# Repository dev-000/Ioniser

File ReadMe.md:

# Build an Ioniser in under $10

This repo contains all the hardware files needed to build a low cost ioniser. It helps in settling dust particles around the device, effectively "cleansing" the air in the room.  Repo also contains the simulation files if you want to check the theoretical output voltages.

Details and circuit explanations are mentioned in the link below. Please do read the links fully before starting the build process. 
 - [http://amaldev.blog/build-ioniser-in-under-10-dollars/](http://amaldev.blog/build-ioniser-in-under-10-dollars/)
 - [http://amaldev.blog/build-an-ioniser-in-under-10-dollars-part-2/](http://amaldev.blog/build-an-ioniser-in-under-10-dollars-part-2/)

Repo contains files for both Positive and Negative Ioniser which gives you a High Voltage positive and negative DC voltages. The circuits are very similar except that the diodes are swapped. Bill of Materials remains same for both versions. 

You can upload the *Gerbers.zip* file directly on to any online PCB manufacturing shop to get it made or edit the Eagle schematic and layout files to your liking.   

Please be very careful dealing with AC voltages and High voltage DC outputs. Capacitors do retain charge for sometime and you will get a zap if you touch them. 

**License:** Released as open source hardware. Do whatever you want with it. :smiley:

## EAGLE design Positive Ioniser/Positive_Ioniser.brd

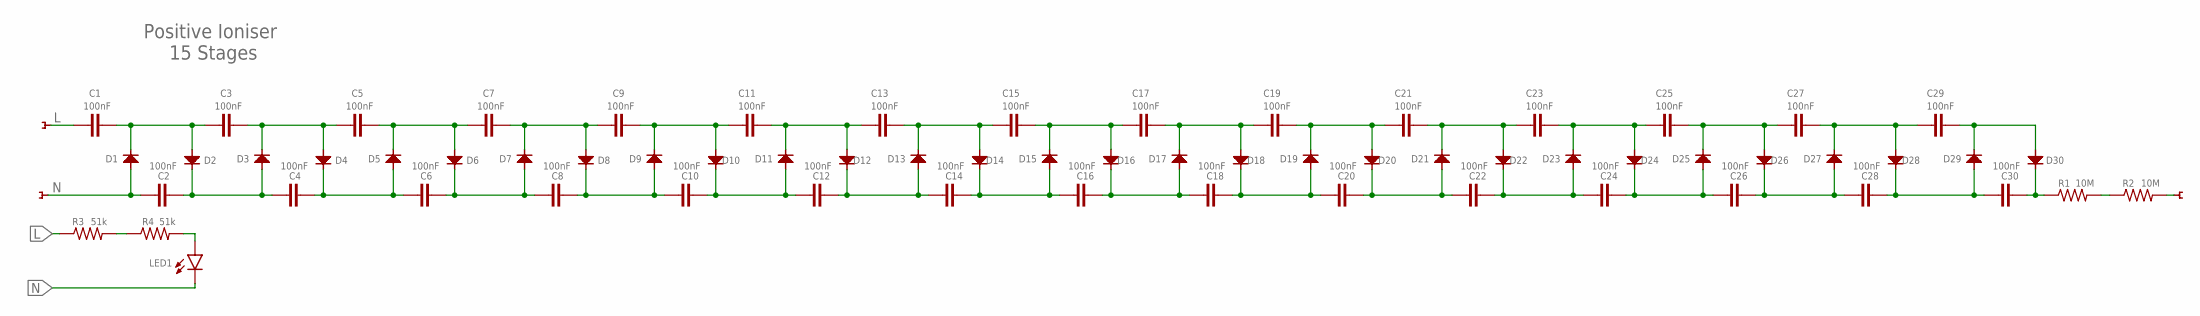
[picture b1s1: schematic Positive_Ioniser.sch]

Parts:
C1, C2, C3, C4, C5, C6, C7, C8, C9, C10, C11, C12, C13, C14, C15, C16, C17, C18, C19, C20, C21, C22, C23, C24, C25, C26, C27, C28, C29, C30: 100nF; C1812; TOLERANCE ±10%; PART-NUM 1812B104K631CT
D1, D2, D3, D4, D5, D6, D7, D8, D9, D10, D11, D12, D13, D14, D15, D16, D17, D18, D19, D20, D21, D22, D23, D24, D25, D26, D27, D28, D29, D30: DIODE-1N4007; DO-214A; PART-NUM 1N4007G
LED1: LED-0603-SMD; LED-0603; PART-NUM D-060306R1/SS2/L
R1, R2: 10M; R1206; TOLERANCE ±1%; PART-NUM 1206W4F1005T5E
R3, R4: 51k; R1210; TOLERANCE ±5%; PART-NUM CR1210J51K0P05Z
TP1, TP2: TEST-POINT5MM; SMD-SQ-PADS-5MM
TP3: TEST-POINT30X10; LONG-RECT-PAD-50MM

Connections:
L: C1.1, R3.1, TP1.P$1
N: C2.1, D1.ANODE (A), LED1.C, TP2.P$1
unnamed: C2.2, C4.1, D2.CATHODE (C), D3.ANODE (A)
unnamed: C1.2, C3.1, D1.CATHODE (C), D2.ANODE (A)
unnamed: R3.2, R4.1
unnamed: R1.2, R2.1
unnamed: C5.2, C7.1, D5.CATHODE (C), D6.ANODE (A)
unnamed: C4.2, C6.1, D4.CATHODE (C), D5.ANODE (A)
unnamed: LED1.A, R4.2
unnamed: C6.2, C8.1, D6.CATHODE (C), D7.ANODE (A)
unnamed: C3.2, C5.1, D3.CATHODE (C), D4.ANODE (A)
unnamed: C9.2, C11.1, D9.CATHODE (C), D10.ANODE (A)
unnamed: C8.2, C10.1, D8.CATHODE (C), D9.ANODE (A)
unnamed: C10.2, C12.1, D10.CATHODE (C), D11.ANODE (A)
unnamed: C7.2, C9.1, D7.CATHODE (C), D8.ANODE (A)
unnamed: C13.2, C15.1, D13.CATHODE (C), D14.ANODE (A)
unnamed: C12.2, C14.1, D12.CATHODE (C), D13.ANODE (A)
unnamed: C14.2, C16.1, D14.CATHODE (C), D15.ANODE (A)
unnamed: C11.2, C13.1, D11.CATHODE (C), D12.ANODE (A)
unnamed: C17.2, C19.1, D17.CATHODE (C), D18.ANODE (A)
unnamed: C16.2, C18.1, D16.CATHODE (C), D17.ANODE (A)
unnamed: C18.2, C20.1, D18.CATHODE (C), D19.ANODE (A)
unnamed: C15.2, C17.1, D15.CATHODE (C), D16.ANODE (A)
unnamed: C21.2, C23.1, D21.CATHODE (C), D22.ANODE (A)
unnamed: C20.2, C22.1, D20.CATHODE (C), D21.ANODE (A)
unnamed: C22.2, C24.1, D22.CATHODE (C), D23.ANODE (A)
unnamed: C19.2, C21.1, D19.CATHODE (C), D20.ANODE (A)
unnamed: C25.2, C27.1, D25.CATHODE (C), D26.ANODE (A)
unnamed: C24.2, C26.1, D24.CATHODE (C), D25.ANODE (A)
unnamed: C26.2, C28.1, D26.CATHODE (C), D27.ANODE (A)
unnamed: C23.2, C25.1, D23.CATHODE (C), D24.ANODE (A)
unnamed: C27.2, C29.1, D27.CATHODE (C), D28.ANODE (A)
unnamed: C28.2, C30.1, D28.CATHODE (C), D29.ANODE (A)
unnamed: C29.2, D29.CATHODE (C), D30.ANODE (A)
unnamed: C30.2, D30.CATHODE (C), R1.1
OUTPUT: R2.2, TP3.1

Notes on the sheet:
15 Stages
Positive Ioniser

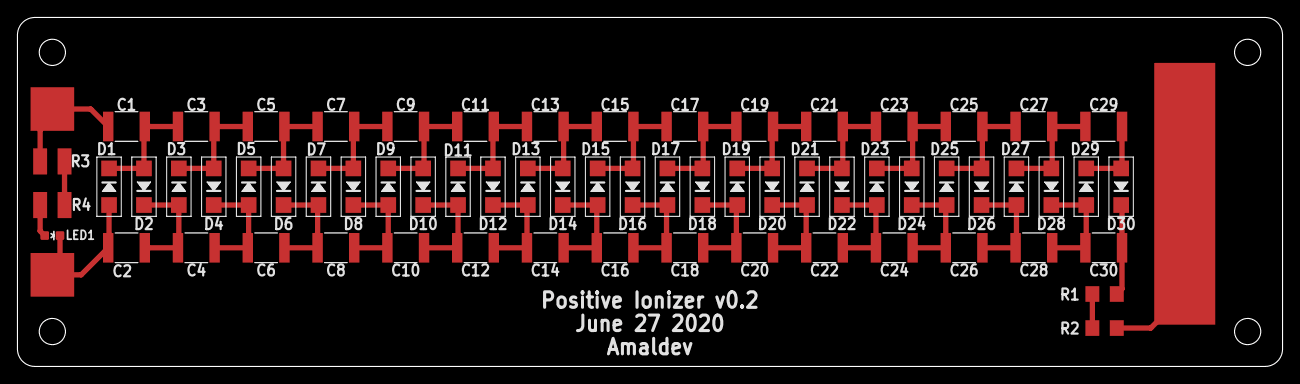
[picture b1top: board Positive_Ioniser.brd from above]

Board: 2 copper layers, 145.0 x 40.0 mm, 68 parts (0 on the bottom side), 36 nets.

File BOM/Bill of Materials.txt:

Qty Value           Device          Package            Parts                                                                                                                                       Description I-RATING PART-NUM         RATED TOLERANCE V-RATING
30  100nF           CAPACITOR-1812  C1812              C1, C2, C3, C4, C5, C6, C7, C8, C9, C10, C11, C12, C13, C14, C15, C16, C17, C18, C19, C20, C21, C22, C23, C24, C25, C26, C27, C28, C29, C30                      1812B104K631CT   630V  ±10%              
2   10M             RESISTOR-1206   R1206              R1, R2                                                                                                                                                           1206W4F1005T5E   0.25W ±1%               
2   51k             RESISTOR-1210   R1210              R3, R4                                                                                                                                                           CR1210J51K0P05Z  0.5W  ±5%               
30  DIODE-1N4007    DIODE-1N4007    DO-214A            D1, D2, D3, D4, D5, D6, D7, D8, D9, D10, D11, D12, D13, D14, D15, D16, D17, D18, D19, D20, D21, D22, D23, D24, D25, D26, D27, D28, D29, D30             1A       1N4007G                          1kV     
1   LED-0603-SMD    LED-0603-SMD    LED-0603           LED1                                                                                                                                                             D-060306R1/SS2/L                         


Other Mechanical Parts:


1 unit:  3mm Acrylic Cover (Laser Cut) - FileName for laser cutting Acrylic-Cover-Laser-Cut.dxf              
4 units: 20mm(long) spacer/Standoff - Nylon Screws (LCSC Part Number: C242804)
4 units: M3 x 5mm(long) - Nylon Screws (LCSC Part Number: C194616)

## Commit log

2020-06-28 Update Links
